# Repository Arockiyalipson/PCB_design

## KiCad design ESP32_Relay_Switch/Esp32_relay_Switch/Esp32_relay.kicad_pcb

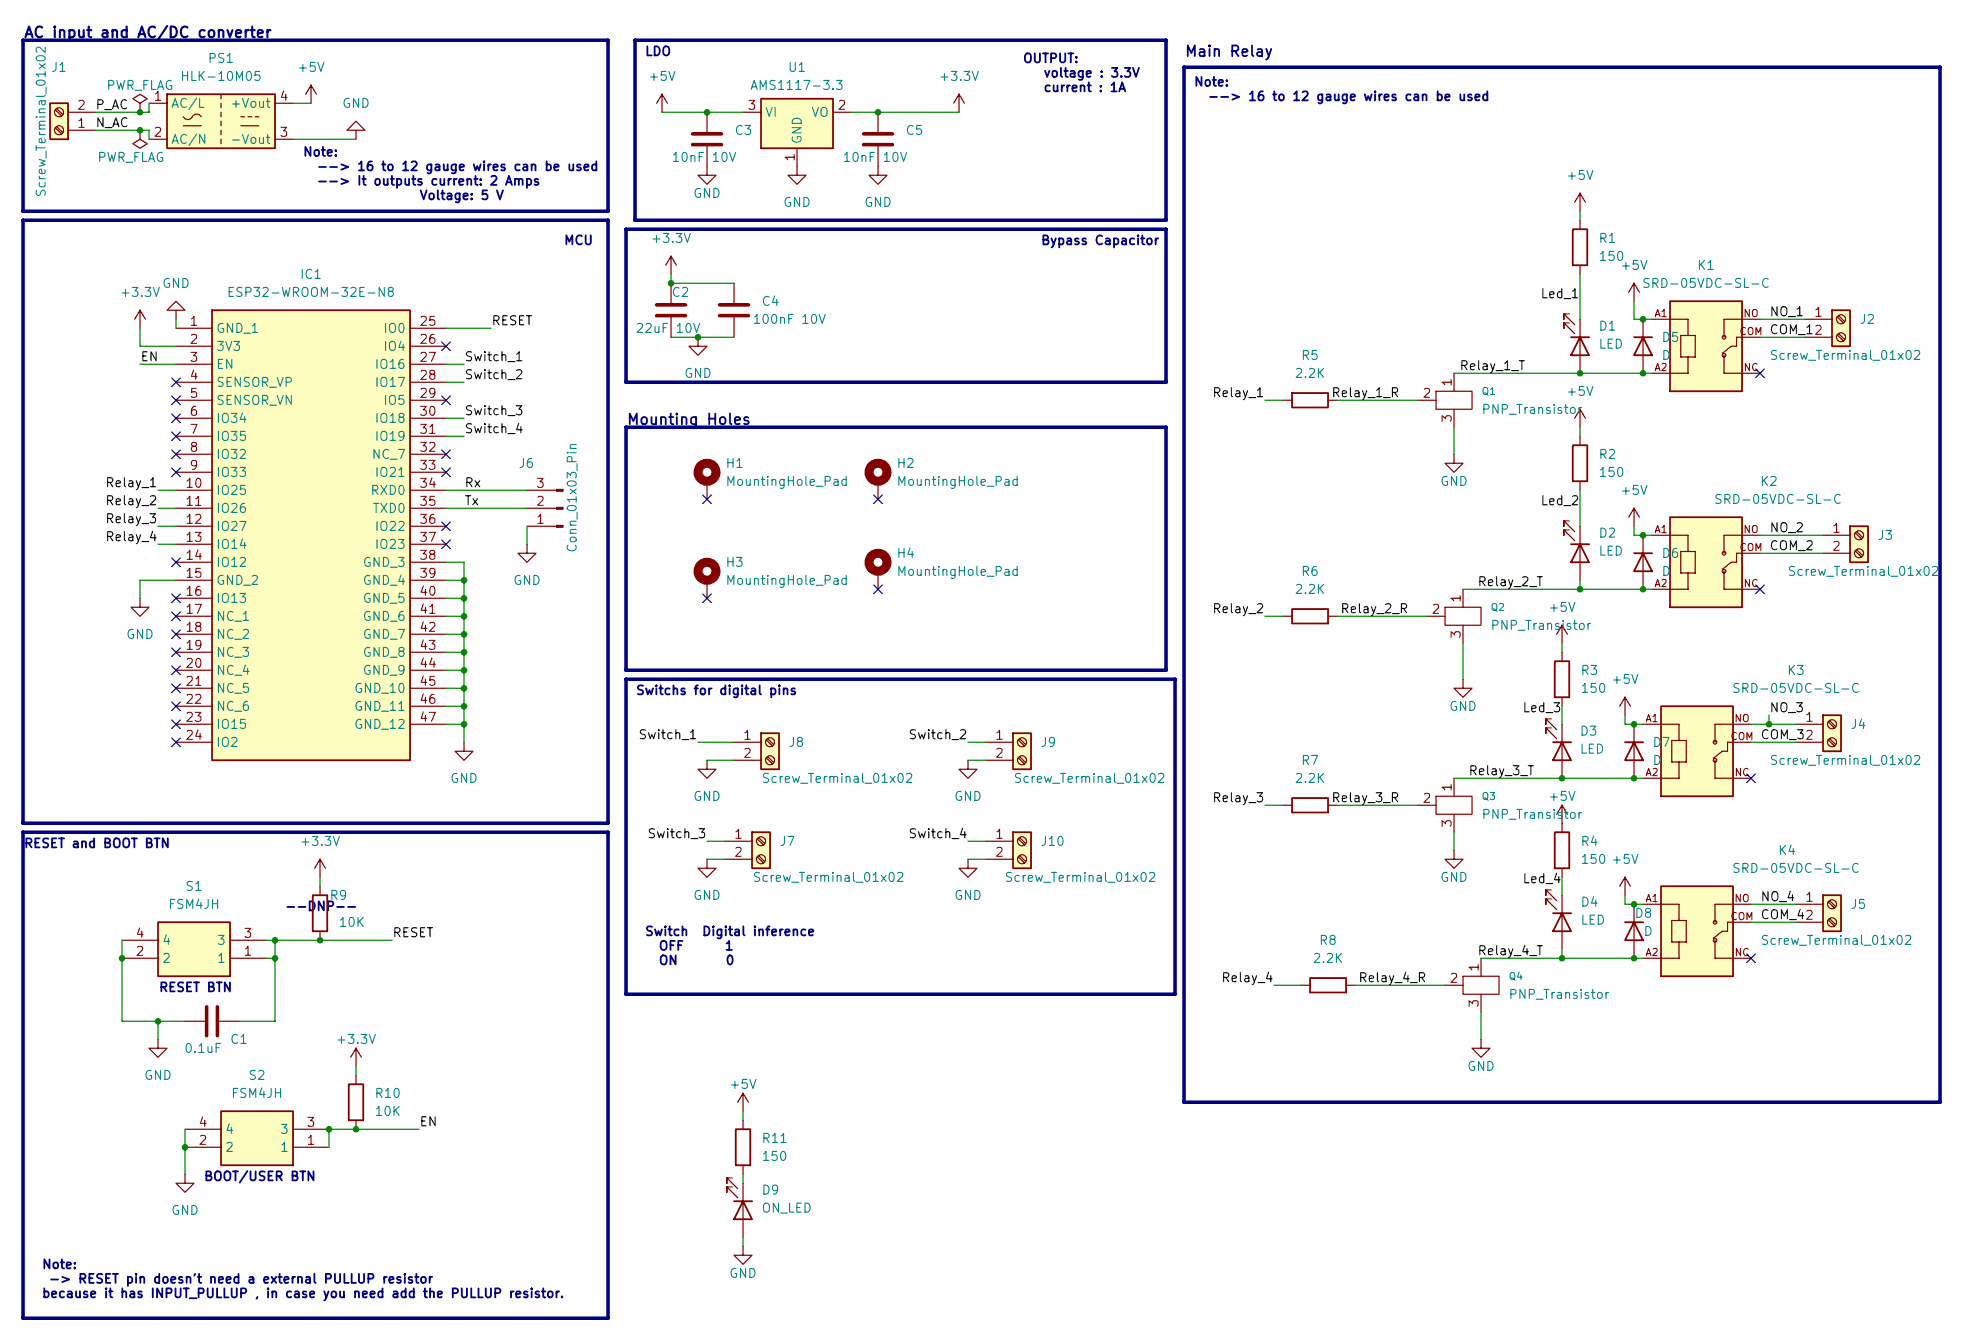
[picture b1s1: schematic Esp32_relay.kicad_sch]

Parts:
C1: 0.1uF; C_0805_2012Metric; Manufacturer_Part_Number C0805C104J8RACTU
C2: 22uF 10V; C_0805_2012Metric; Manufacturer_Part_Number CL21A226MPQNNNE
C3, C5: 10nF 10V; C_0805_2012Metric; Manufacturer_Part_Number 885012007009
C4: 100nF 10V; C_0805_2012Metric; Manufacturer_Part_Number C0805C104J5RAC
D1, D2, D3, D4: LED; LED_1206_3216Metric; Manufacturer_Part_Number 156120VS75000
D5, D6, D7, D8: D; D_0805_2012Metric; Manufacturer_Part_Number BZY55C9V1 RBG
D9: ON_LED; LED_1206_3216Metric; Manufacturer_Part_Number 156120VS75000
H1, H2, H3, H4: MountingHole_Pad; MountingHole_2.5mm_Pad; Manufacturer_Part_Number ----
IC1: ESP32-WROOM-32E-N8; ESP32WROOM32EN8; Mouser Part Number 356-ESP32WRM32E164PH
J1, J2, J3, J4, J5, J7, J8, J9, J10: Screw_Terminal_01x02; TerminalBlock_MetzConnect_Type175_RT02702HBLC_1x02_P7.50mm_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
J6: Conn_01x03_Pin; PinHeader_1x03_P2.54mm_Vertical; Manufacturer_Part_Number ----
K1, K2, K3, K4: SRD-05VDC-SL-C; RELAY_SRD-05VDC-SL-C; Manufacturer_Part_Number SRD-05VDC-SL-C
PS1: HLK-10M05; Converter_ACDC_HiLink_HLK-10Mxx; Manufacturer_Part_Number RW-317
Q1, Q2, Q3, Q4: PNP_Transistor; SOT-23; Manufacturer_Part_Number 5203
R1, R2, R3, R4, R11: 150; R_0805_2012Metric; Manufacturer_Part_Number CRCW0805150RFKEAC
R5, R6, R7, R8: 2.2K; R_0805_2012Metric; Manufacturer_Part_Number CRCW08052K20FKEA
R9, R10: 10K; R_0805_2012Metric; Manufacturer_Part_Number CR0805-FX-1002ELF
S1, S2: FSM4JH; Mouser Part Number 506-FSM4JH
U1: AMS1117-3.3; SOT-223-3_TabPin2; Manufacturer_Part_Number AMS1117-3.3

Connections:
+3.3V: C2.1, C4.1, C5.1, IC1.2 (3V3), R9.1, R10.1, U1.2 (VO)
+5V: C3.1, D5.1 (K), D6.1 (K), D7.1 (K), D8.1 (K), K1.A1, K2.A1, K3.A1, K4.A1, PS1.4 (+Vout), R1.1, R2.1, R3.1, R4.1, R11.1, U1.3 (VI)
/COM_1: J2.2, K1.COM
/COM_2: J3.2, K2.COM
/COM_3: J4.2, K3.COM
/COM_4: J5.2, K4.COM
/EN: IC1.3 (EN), R10.2, S2.1, S2.3
/Led_1: D1.1 (K), R1.2
/Led_2: D2.1 (K), R2.2
/Led_3: D3.1 (K), R3.2
/Led_4: D4.1 (K), R4.2
/NO_1: J2.1, K1.NO
/NO_2: J3.1, K2.NO
/NO_3: J4.1, K3.NO
/NO_4: J5.1, K4.NO
/N_AC: J1.1, PS1.2 (AC/N)
/P_AC: J1.2, PS1.1 (AC/L)
/RESET: C1.2, IC1.25 (IO0), R9.2, S1.1, S1.3
/Relay_1: IC1.10 (IO25), R5.2
/Relay_1_R: Q1.2, R5.1
/Relay_1_T: D1.2 (A), D5.2 (A), K1.A2, Q1.1
/Relay_2: IC1.11 (IO26), R6.1
/Relay_2_R: Q2.2, R6.2
/Relay_2_T: D2.2 (A), D6.2 (A), K2.A2, Q2.1
/Relay_3: IC1.12 (IO27), R7.1
/Relay_3_R: Q3.2, R7.2
/Relay_3_T: D3.2 (A), D7.2 (A), K3.A2, Q3.1
/Relay_4: IC1.13 (IO14), R8.1
/Relay_4_R: Q4.2, R8.2
/Relay_4_T: D4.2 (A), D8.2 (A), K4.A2, Q4.1
/Rx: IC1.34 (RXD0), J6.3
/Switch_1: IC1.27 (IO16), J8.1
/Switch_2: IC1.28 (IO17), J9.1
/Switch_3: IC1.30 (IO18), J7.1
/Switch_4: IC1.31 (IO19), J10.1
/Tx: IC1.35 (TXD0), J6.2
GND: C1.1, C2.2, C3.2, C4.2, C5.2, D9.2 (A), IC1.1 (GND_1), IC1.15 (GND_2), IC1.38 (GND_3), IC1.39 (GND_4), IC1.40 (GND_5), IC1.41 (GND_6), IC1.42 (GND_7), IC1.43 (GND_8), IC1.44 (GND_9), IC1.45 (GND_10), IC1.46 (GND_11), IC1.47 (GND_12), J6.1, J7.2, J8.2, J9.2, J10.2, PS1.3 (-Vout), Q1.3, Q2.3, Q3.3, Q4.3, S1.2, S1.4, S2.2, S2.4, U1.1 (GND)
unnamed: D9.1 (K), R11.2

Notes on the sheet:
Note: -> RESET pin doesn't need a external PULLUP resistor because it has INPUT_PULLUP , in case you need add the PULLUP resistor.
Main Relay
AC input and AC/DC converter
OUTPUT: voltage : 3.3V current : 1A
Switch Digital inference OFF 1 ON 0
RESET BTN
RESET and BOOT BTN
Switchs for digital pins
Note: --> 16 to 12 gauge wires can be used --> It outputs current: 2 Amps Voltage: 5 V
Note: --> 16 to 12 gauge wires can be used
Mounting Holes
--DNP--
Bypass Capacitor
MCU
LDO
BOOT/USER BTN

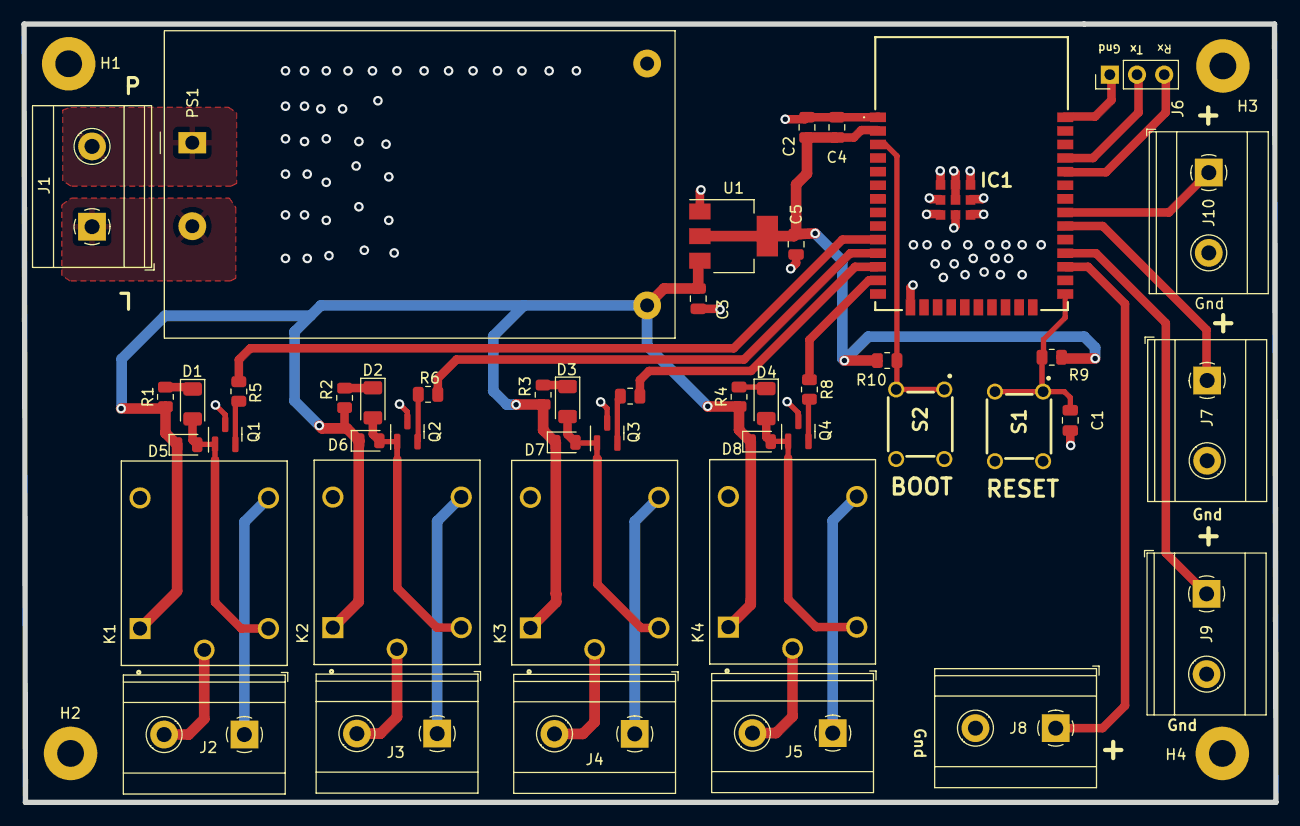
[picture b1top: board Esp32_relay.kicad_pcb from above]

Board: 2 copper layers, 117.0 x 72.7 mm, 50 parts (0 on the bottom side), 37 nets.

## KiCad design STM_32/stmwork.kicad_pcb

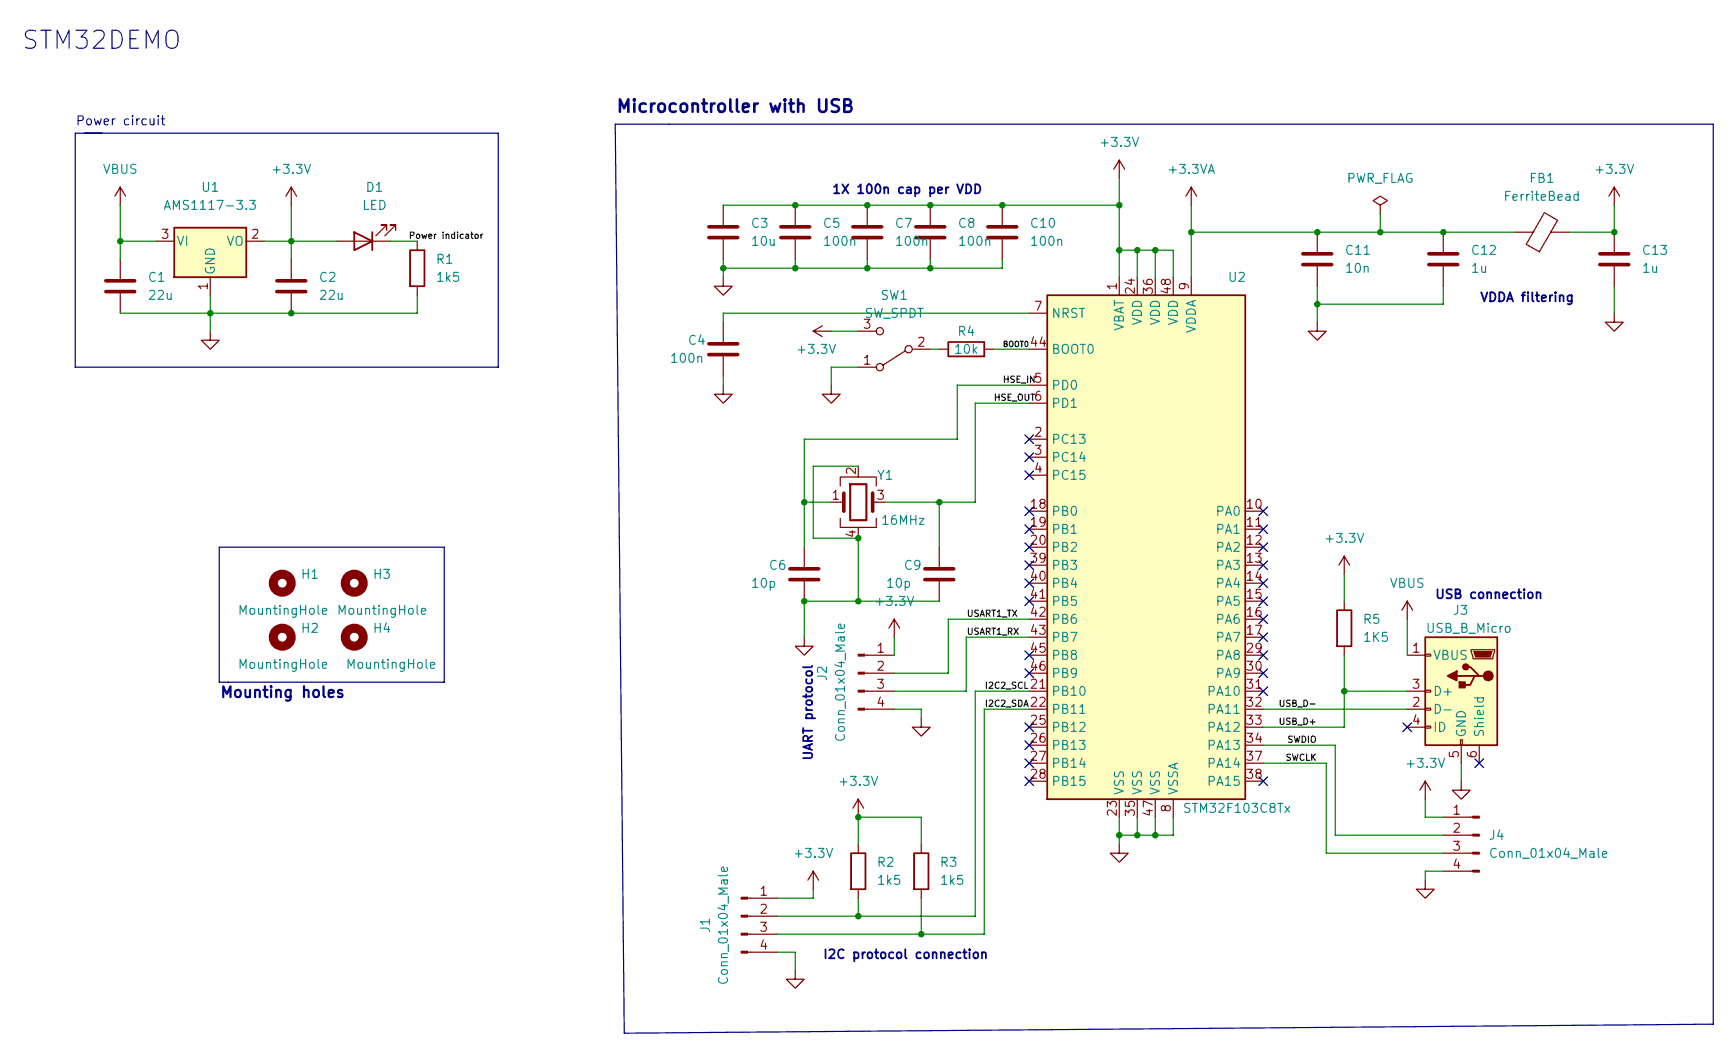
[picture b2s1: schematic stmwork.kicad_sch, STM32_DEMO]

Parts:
C1, C2: 22u; C_0805_2012Metric
C3: 10u; C_0603_1608Metric
C4, C5, C7, C8, C10: 100n; C_0603_1608Metric
C6, C9: 10p; C_0603_1608Metric
C11: 10n; C_0603_1608Metric
C12, C13: 1u; C_0603_1608Metric
D1: LED; LED_0603_1608Metric
FB1: FerriteBead; L_0603_1608Metric
H1, H2, H3, H4: MountingHole; MountingHole_2.1mm
J1, J2, J4: Conn_01x04_Male; PinHeader_1x04_P2.54mm_Vertical
J3: USB_B_Micro; USB_Micro-B_Wuerth_629105150521
R1, R2, R3: 1k5; R_0402_1005Metric
R4: 10k; R_0402_1005Metric
R5: 1K5; R_0402_1005Metric
SW1: SW_SPDT; SW_SPDT_PCM12
U1: AMS1117-3.3; SOT-223-3_TabPin2
U2: STM32F103C8Tx; LQFP-48_7x7mm_P0.5mm
Y1: 16MHz; Crystal_SMD_3225-4Pin_3.2x2.5mm

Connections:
+3.3V: C2.1, C3.1, C5.1, C7.1, C8.1, C10.1, C13.1, D1.2 (A), FB1.2, J1.1, J2.1, J4.1, R2.1, R3.1, R5.1, SW1.3 (C), U1.2 (VO), U2.1 (VBAT), U2.24 (VDD), U2.36 (VDD), U2.48 (VDD)
+3.3VA: C11.1, C12.2, FB1.1, U2.9 (VDDA)
/BOOT0: R4.2, U2.44 (BOOT0)
/HSE_IN: C6.1, U2.5 (PD0), Y1.1
/HSE_OUT: C9.1, U2.6 (PD1), Y1.3
/I2C2_SCL: J1.2, R2.2, U2.21 (PB10)
/I2C2_SDA: J1.3, R3.2, U2.22 (PB11)
/Power indicator: D1.1 (K), R1.1
/SWCLK: J4.3, U2.37 (PA14)
/SWDIO: J4.2, U2.34 (PA13)
/USART1_RX: J2.3, U2.43 (PB7)
/USART1_TX: J2.2, U2.42 (PB6)
/USB_D+: J3.3 (D+), R5.2, U2.33 (PA12)
/USB_D-: J3.2 (D-), U2.32 (PA11)
GND: C1.2, C2.2, C3.2, C4.2, C5.2, C6.2, C7.2, C8.2, C9.2, C10.2, C11.2, C12.1, C13.2, J1.4, J2.4, J3.5 (GND), J4.4, R1.2, SW1.1 (A), U1.1 (GND), U2.8 (VSSA), U2.23 (VSS), U2.35 (VSS), U2.47 (VSS), Y1.2, Y1.4
unnamed: C4.1, U2.7 (NRST)
unnamed: R4.1, SW1.2 (B)
VBUS: C1.1, J3.1 (VBUS), U1.3 (VI)

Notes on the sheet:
Microcontroller with USB
USB connection
VDDA filtering
I2C protocol connection
Power circuit
STM32DEMO
UART protocol
Mounting holes
1X 100n cap per VDD

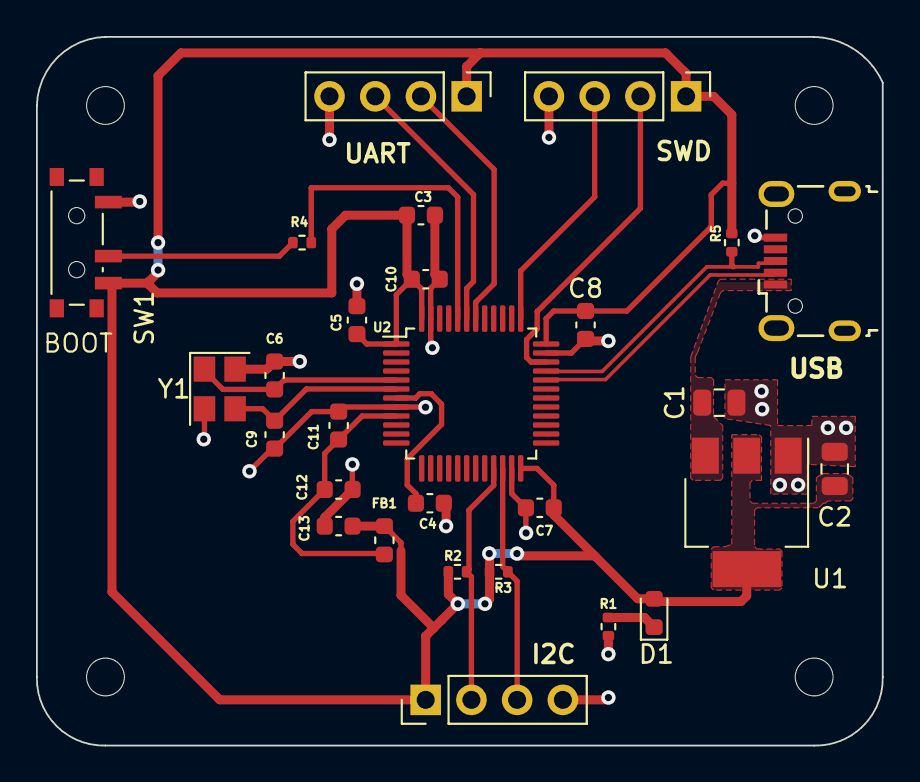
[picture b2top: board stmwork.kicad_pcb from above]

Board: 2 copper layers, 47.0 x 39.4 mm, 32 parts (0 on the bottom side), 18 nets.

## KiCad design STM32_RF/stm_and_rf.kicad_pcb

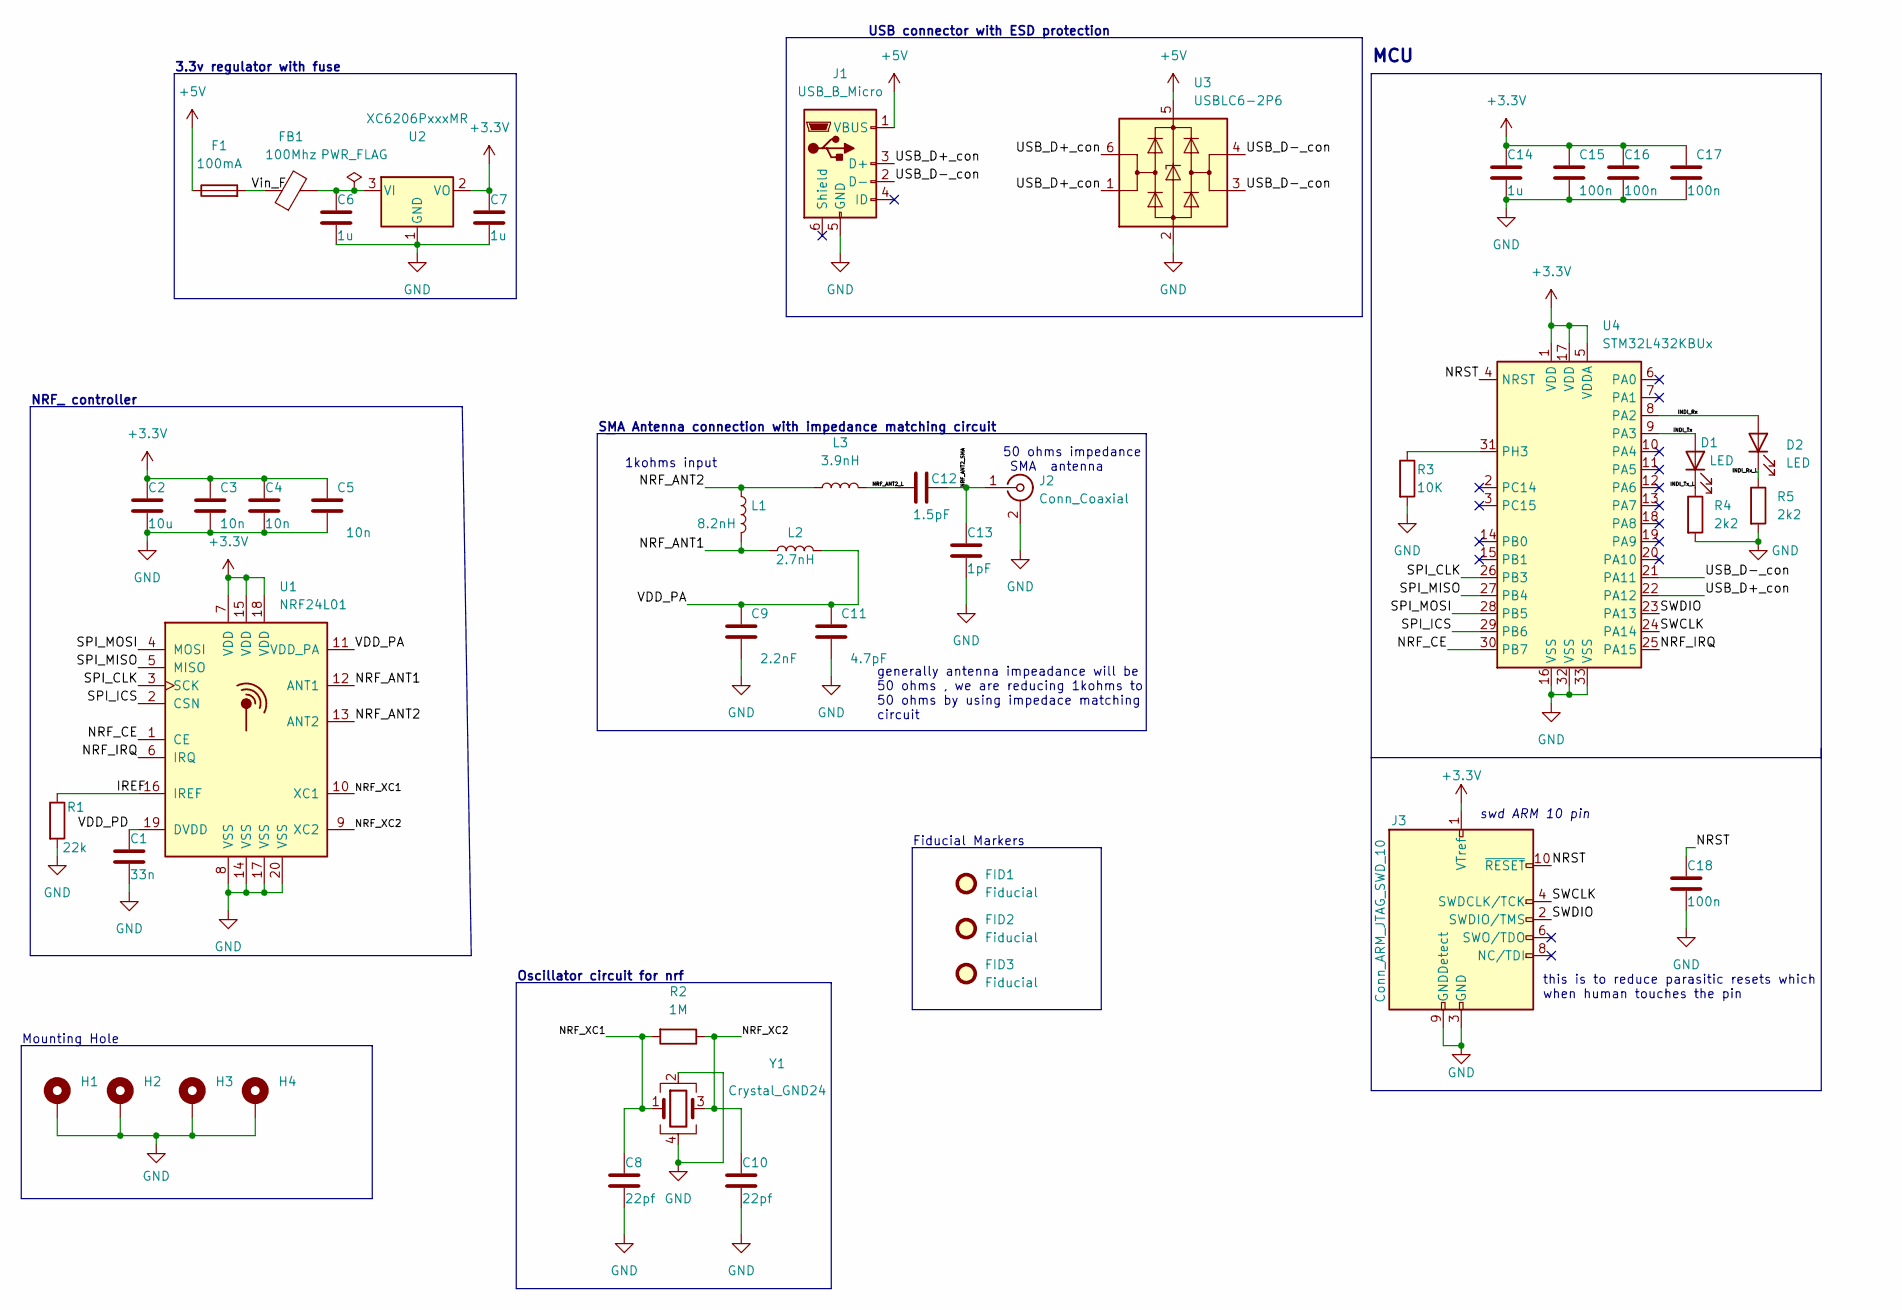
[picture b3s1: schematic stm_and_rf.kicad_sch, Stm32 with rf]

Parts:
C1: 33n; C_0402_1005Metric
C2: 10u; C_0402_1005Metric
C3, C4, C5: 10n; C_0402_1005Metric
C6, C7: 1u; C_0603_1608Metric
C8, C10: 22pf; C_0402_1005Metric
C9: 2.2nF; C_0402_1005Metric
C11: 4.7pF; C_0402_1005Metric
C12: 1.5pF; C_0402_1005Metric
C13: 1pF; C_0402_1005Metric
C14: 1u; C_0402_1005Metric
C15, C16, C17, C18: 100n; C_0402_1005Metric
D1, D2: LED; LED_0603_1608Metric
F1: 100mA; Fuse_1206_3216Metric
FB1: 100Mhz; L_0805_2012Metric
FID1, FID2, FID3: Fiducial; Fiducial_0.5mm_Mask1mm
H1, H2, H3, H4: MountingHole_Pad; MountingHole_2.2mm_M2_Pad
J1: USB_B_Micro; USB_Micro-B_Wuerth_629105150521
J2: Conn_Coaxial; SMA_Samtec_SMA-J-P-X-ST-EM1_EdgeMount
J3: Conn_ARM_JTAG_SWD_10; PinHeader_2x05_P1.27mm_Vertical
L1: 8.2nH; L_0402_1005Metric
L2: 2.7nH; L_0402_1005Metric
L3: 3.9nH; L_0402_1005Metric
R1: 22k; R_0402_1005Metric
R2: 1M; R_0402_1005Metric
R3: 10K; R_0402_1005Metric
R4, R5: 2k2; R_0402_1005Metric
U1: NRF24L01; QFN-20-1EP_4x4mm_P0.5mm_EP2.5x2.5mm
U2: XC6206PxxxMR; SOT-23
U3: USBLC6-2P6; SOT-666
U4: STM32L432KBUx; QFN-32-1EP_5x5mm_P0.5mm_EP3.45x3.45mm
Y1: Crystal_GND24; Crystal_SMD_3225-4Pin_3.2x2.5mm

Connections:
+3.3V: C2.1, C3.1, C4.1, C5.1, C7.1, C14.1, C15.1, C16.1, C17.1, J3.1 (VTref), U1.7 (VDD), U1.15 (VDD), U1.18 (VDD), U2.2 (VO), U4.1 (VDD), U4.5 (VDDA), U4.17 (VDD)
+5V: F1.1, J1.1 (VBUS), U3.5 (VBUS)
/INDI_Rx: D2.2 (A), U4.8 (PA2)
/INDI_Rx_L: D2.1 (K), R5.1
/INDI_Tx: D1.2 (A), U4.9 (PA3)
/INDI_Tx_L: D1.1 (K), R4.1
/IREF: R1.1, U1.16 (IREF)
/NRF_ANT1: L1.2, L2.1, U1.12 (ANT1)
/NRF_ANT2: L1.1, L3.1, U1.13 (ANT2)
/NRF_ANT2_L: C12.2, L3.2
/NRF_ANT2_SMA: C12.1, C13.1, J2.1 (In)
/NRF_CE: U1.1 (CE), U4.30 (PB7)
/NRF_IRQ: U1.6 (IRQ), U4.25 (PA15)
/NRF_XC1: C8.1, R2.2, U1.10 (XC1), Y1.1
/NRF_XC2: C10.1, R2.1, U1.9 (XC2), Y1.3
/NRST: C18.1, J3.10 (~RESET), U4.4 (NRST)
/SPI_CLK: U1.3 (SCK), U4.26 (PB3)
/SPI_ICS: U1.2 (CSN), U4.29 (PB6)
/SPI_MISO: U1.5 (MISO), U4.27 (PB4)
/SPI_MOSI: U1.4 (MOSI), U4.28 (PB5)
/SWCLK: J3.4 (SWDCLK/TCK), U4.24 (PA14)
/SWDIO: J3.2 (SWDIO/TMS), U4.23 (PA13)
/USB_D+_con: J1.3 (D+), U3.1 (I/O1), U3.6 (I/O1), U4.22 (PA12)
/USB_D-_con: J1.2 (D-), U3.3 (I/O2), U3.4 (I/O2), U4.21 (PA11)
/VDD_PA: C9.1, C11.1, L2.2, U1.11 (VDD_PA)
/VDD_PD: C1.1, U1.19 (DVDD)
/Vin_F: F1.2, FB1.1
GND: C1.2, C2.2, C3.2, C4.2, C5.2, C6.2, C7.2, C8.2, C9.2, C10.2, C11.2, C13.2, C14.2, C15.2, C16.2, C17.2, C18.2, H1.1, H2.1, H3.1, H4.1, J1.5 (GND), J2.2 (Ext), J3.3 (GND), J3.5 (GND), J3.9 (GNDDetect), R1.2, R3.2, R4.2, R5.2, U1.8 (VSS), U1.14 (VSS), U1.17 (VSS), U1.20 (VSS), U2.1 (GND), U3.2 (GND), U4.16 (VSS), U4.32 (VSS), U4.33 (VSS), Y1.2, Y1.4
unnamed: C6.1, FB1.2, U2.3 (VI)
unnamed: R3.1, U4.31 (PH3)

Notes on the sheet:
1kohms input
Fiducial Markers
swd ARM 10 pin
generally antenna impeadance will be 50 ohms , we are reducing 1kohms to 50 ohms by using impedace matching circuit
3.3v regulator with fuse
Mounting Hole
SMA Antenna connection with impedance matching circuit
MCU
USB connector with ESD protection
Oscillator circuit for nrf
this is to reduce parasitic resets which when human touches the pin
50 ohms impedance SMA antenna
NRF_ controller

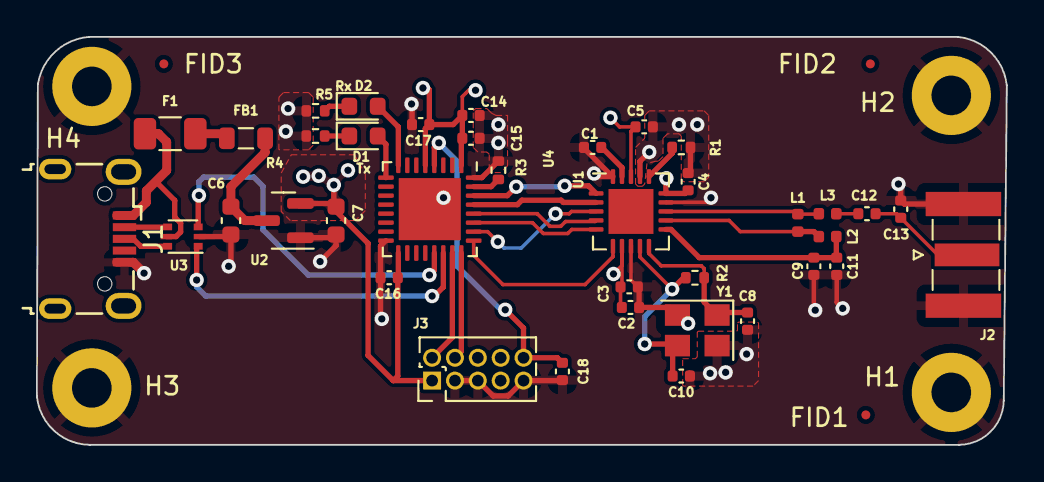
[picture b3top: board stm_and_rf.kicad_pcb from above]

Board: 4 copper layers, 53.9 x 22.7 mm, 45 parts (0 on the bottom side), 30 nets.

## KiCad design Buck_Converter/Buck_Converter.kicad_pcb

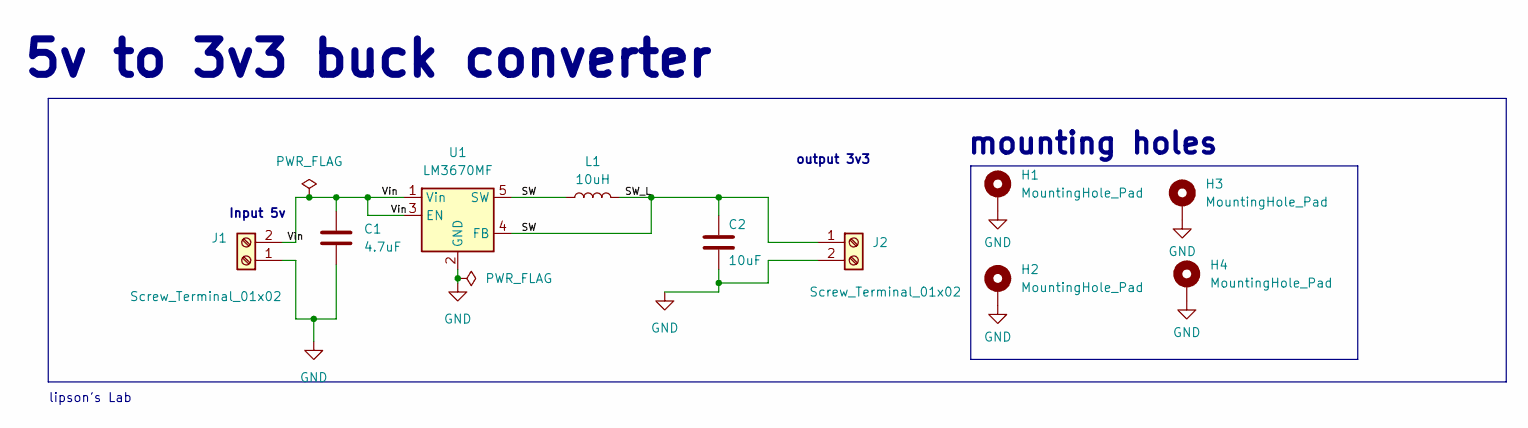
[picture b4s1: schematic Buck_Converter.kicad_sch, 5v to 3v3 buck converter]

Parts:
C1: 4.7uF; C_0805_2012Metric_Pad1.18x1.45mm_HandSolder
C2: 10uF; C_1206_3216Metric_Pad1.33x1.80mm_HandSolder
H1, H2, H3, H4: MountingHole_Pad; MountingHole_2.2mm_M2_DIN965_Pad
J1, J2: Screw_Terminal_01x02; TerminalBlock_Phoenix_MKDS-1,5-2-5.08_1x02_P5.08mm_Horizont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
L1: 10uH; VLCF4024T-100MR90-2
U1: LM3670MF; TSOT-23-5

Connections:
/SW: C2.1, J2.1, L1.1, L1.2, U1.4 (FB), U1.5 (SW)
/Vin: C1.1, J1.2, U1.1 (Vin), U1.3 (EN)
GND: C1.2, C2.2, H1.1, H2.1, H3.1, H4.1, J1.1, J2.2, U1.2 (GND)

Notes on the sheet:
lipson's Lab
Input 5v
output 3v3
mounting holes
5v to 3v3 buck converter

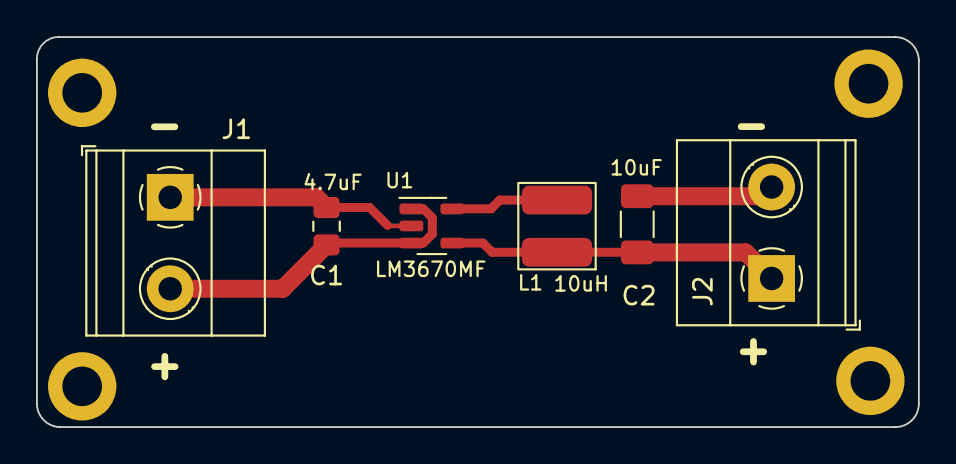
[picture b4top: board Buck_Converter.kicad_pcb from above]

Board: 2 copper layers, 49.0 x 21.7 mm, 10 parts (0 on the bottom side), 3 nets.

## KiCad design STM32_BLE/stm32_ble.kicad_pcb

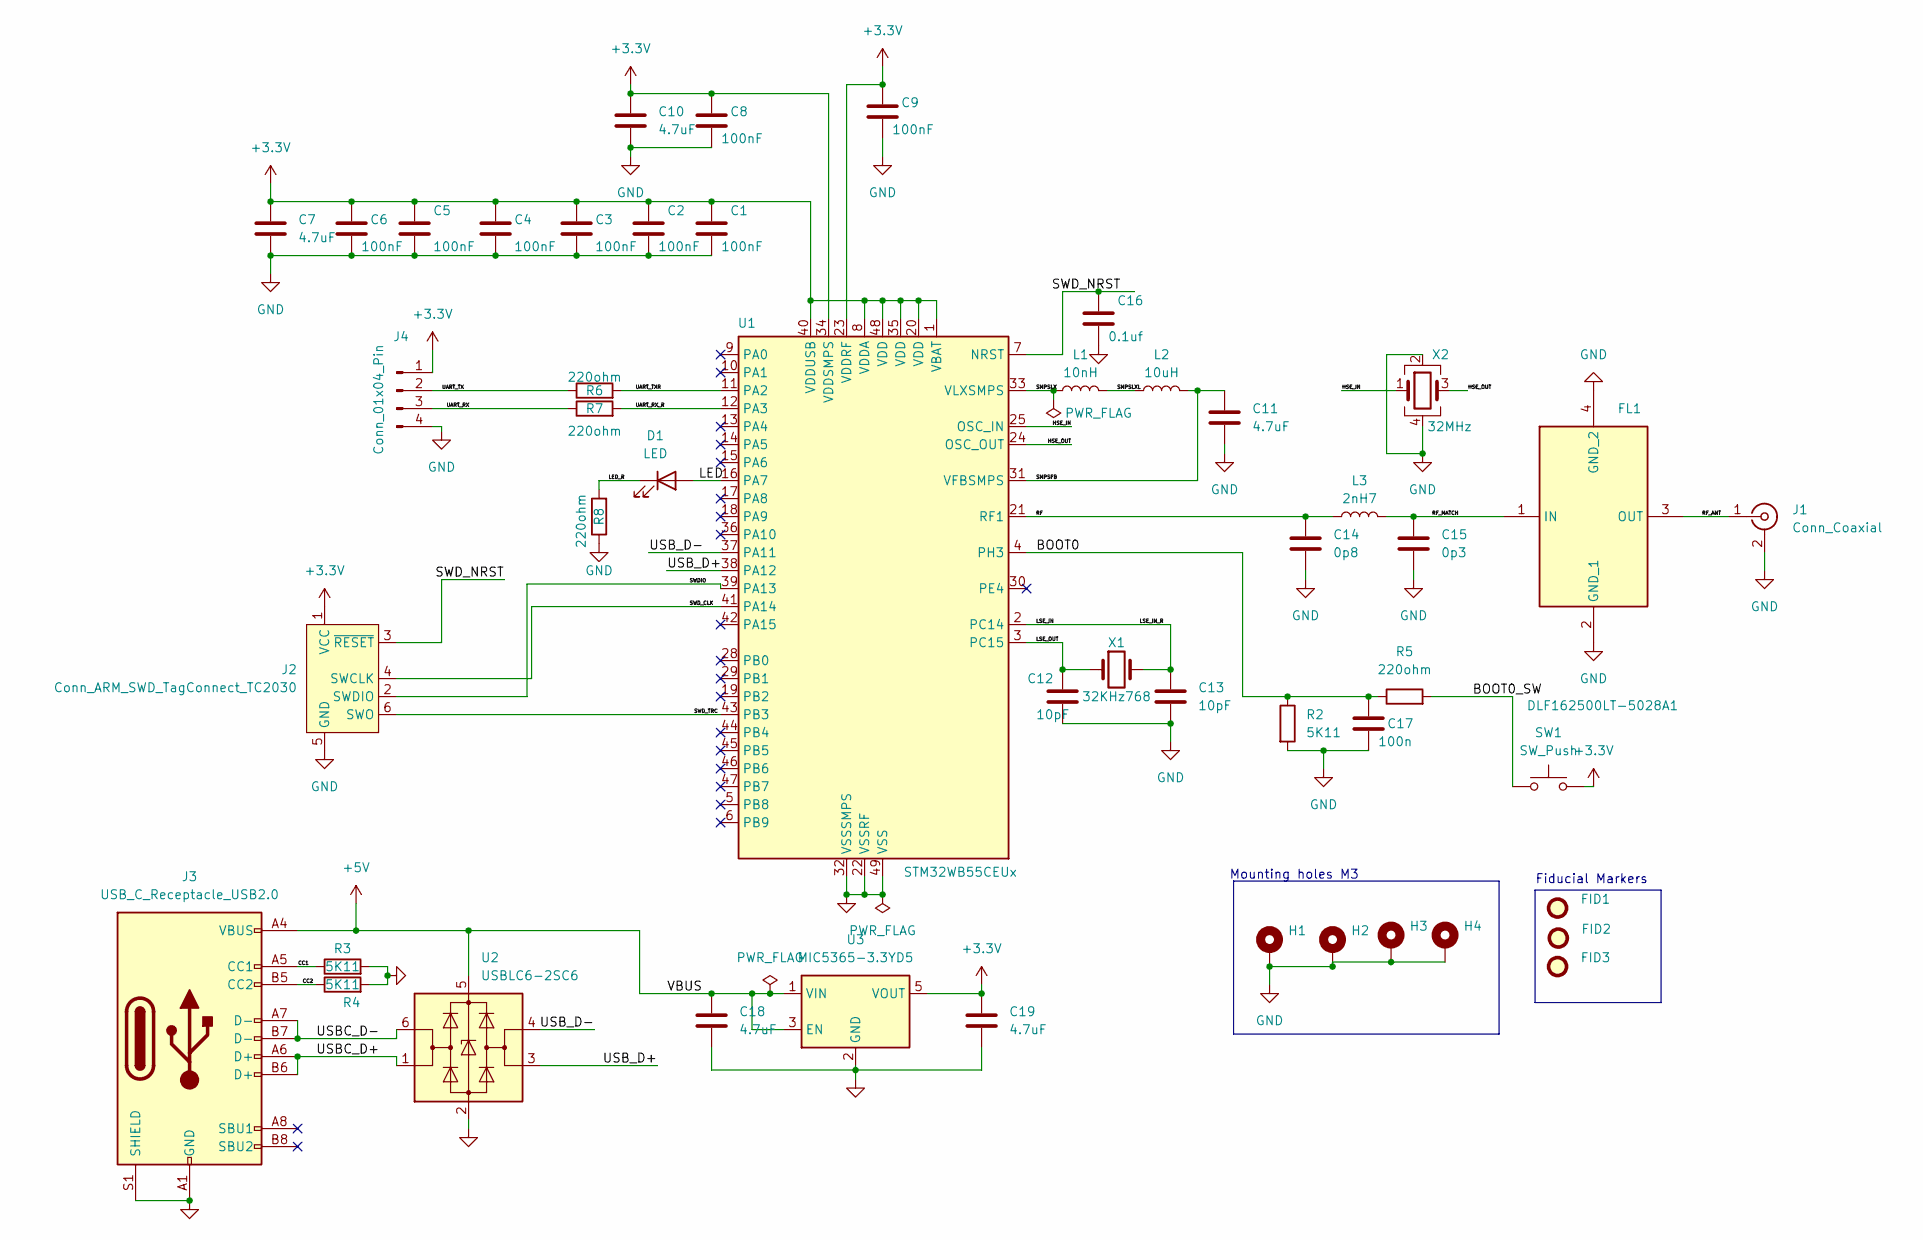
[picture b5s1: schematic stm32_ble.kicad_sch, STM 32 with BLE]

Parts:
C1, C2, C3, C4, C5, C6, C8, C9: 100nF; C_0402_1005Metric; Manufacturer_Part_Number VJ0402Y104KXXCW1BC
C7, C10, C11, C18: 4.7uF; C_0603_1608Metric; Manufacturer_Part_Number GCJ188C70J475KE02D
C12, C13: 10pF; C_0402_1005Metric; Manufacturer_Part_Number C0402C100K4GACAUTO
C14: 0p8; C_0402_1005Metric; Manufacturer_Part_Number GRM0335C1HR80BA01D
C15: 0p3; C_0402_1005Metric; Manufacturer_Part_Number GRM1555C1HR30WA01D
C16: 0.1uf; C_0402_1005Metric; Manufacturer_Part_Number C0402C104K4RACTU
C17: 100n; C_0402_1005Metric; Manufacturer_Part_Number CC0402KRX7R7BB104
C19: 4.7uF; C_0402_1005Metric; Manufacturer_Part_Number GRT155C81A475ME13J
D1: LED; LED_0402_1005Metric; Manufacturer_Part_Number 150040RS73240
FID1, FID2, FID3: Fiducial; Fiducial_1mm_Mask2mm
FL1: DLF162500LT-5028A1; DLF162500LT5028A1; Mouser Part Number 810-DLF16250LT5028A1
H1, H2, H3, H4: MountingHole_Pad; MountingHole_2.2mm_M2_Pad_Via
J1: Conn_Coaxial; U.FL_Hirose_U.FL-R-SMT-1_Vertical; Manufacturer_Part_Number U.FL-R-SMT(01)
J2: Conn_ARM_SWD_TagConnect_TC2030; Tag-Connect_TC2030-IDC-FP_2x03_P1.27mm_Vertical
J3: USB_C_Receptacle_USB2.0; USB_C_Receptacle_GCT_USB4105-xx-A_16P_TopMnt_Horizontal; Manufacturer_Part_Number USB4105-GF-A
J4: Conn_01x04_Pin; Molex_PicoBlade_53048-0410_1x04_P1.25mm_Horizontal; Manufacturer_Part_Number 53048-0410
L1: 10nH; L_0402_1005Metric; Manufacturer_Part_Number LQG15WZ10NJ02D
L2: 10uH; L_0805_2012Metric; Manufacturer_Part_Number LQG15WZ10NJ02D
L3: 2nH7; L_0402_1005Metric; Manufacturer_Part_Number LQG15HS2N7S02D
R2, R3, R4: 5K11; R_0402_1005Metric; Manufacturer_Part_Number RC0402FR-075K1L
R5, R6, R7, R8: 220ohm; R_0402_1005Metric; Manufacturer_Part_Number MCS04020C2200FE000
SW1: SW_Push; SW_SPST_CK_RS282G05A3; Manufacturer_Part_Number RS282G05A3SMRT
U1: STM32WB55CEUx; QFN-48-1EP_7x7mm_P0.5mm_EP5.6x5.6mm; Manufacturer_Part_Number STM32WB55CEU6
U2: USBLC6-2SC6; SOT-23-6; Manufacturer_Part_Number USBLC6-2SC6
U3: MIC5365-3.3YD5; SOT-23-5; Manufacturer_Part_Number MIC5365-3.3YD5-TR
X1: 32KHz768; Crystal_SMD_2012-2Pin_2.0x1.2mm; Manufacturer_Part_Number NX2012SA-32.768K-STD-MUB-1
X2: 32MHz; Crystal_SMD_2016-4Pin_2.0x1.6mm; Manufacturer_Part_Number NX2016SA-32M-EXS00A-CS06465

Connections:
+3.3V: C1.1, C2.1, C3.1, C4.1, C5.1, C6.1, C7.1, C8.1, C9.1, C10.1, C19.1, J2.1 (VCC), J4.1, SW1.2, U1.1 (VBAT), U1.8 (VDDA), U1.20 (VDD), U1.23 (VDDRF), U1.34 (VDDSMPS), U1.35 (VDD), U1.40 (VDDUSB), U1.48 (VDD), U3.5 (VOUT)
+5V: C18.1, J3.A4 (VBUS), J3.A9 (VBUS), J3.B4 (VBUS), J3.B9 (VBUS), U2.5 (VBUS), U3.1 (VIN), U3.3 (EN)
/BOOT0: C17.1, R2.1, R5.1, U1.4 (PH3)
/BOOT0_SW: R5.2, SW1.1
/CC1: J3.A5 (CC1), R3.1
/CC2: J3.B5 (CC2), R4.1
/HSE_IN: U1.25 (OSC_IN), X2.1
/HSE_OUT: U1.24 (OSC_OUT), X2.3
/LED: D1.2 (A), U1.16 (PA7)
/LED_R: D1.1 (K), R8.2
/LSE_IN: C13.1, U1.2 (PC14), X1.2
/LSE_OUT: C12.1, U1.3 (PC15), X1.1
/RF: C14.1, L3.1, U1.21 (RF1)
/RF_ANT: FL1.3 (OUT), J1.1 (In)
/RF_MATCH: C15.1, FL1.1 (IN), L3.2
/SMPSFB: C11.1, L2.2, U1.31 (VFBSMPS)
/SMPSLX: L1.1, U1.33 (VLXSMPS)
/SMPSLXL: L1.2, L2.1
/SWDIO: J2.2 (SWDIO), U1.39 (PA13)
/SWD_CLK: J2.4 (SWCLK), U1.41 (PA14)
/SWD_NRST: C16.1, J2.3 (~RESET), U1.7 (NRST)
/SWD_TRC: J2.6 (SWO), U1.43 (PB3)
/UART_RX: J4.3, R7.1
/UART_RX_R: R7.2, U1.12 (PA3)
/UART_TX: J4.2, R6.1
/UART_TXR: R6.2, U1.11 (PA2)
/USBC_D+: J3.A6 (D+), J3.B6 (D+), U2.1 (I/O1)
/USBC_D-: J3.A7 (D-), J3.B7 (D-), U2.6 (I/O1)
/USB_D+: U1.38 (PA12), U2.3 (I/O2)
/USB_D-: U1.37 (PA11), U2.4 (I/O2)
GND: C1.2, C2.2, C3.2, C4.2, C5.2, C6.2, C7.2, C8.2, C9.2, C10.2, C11.2, C12.2, C13.2, C14.2, C15.2, C16.2, C17.2, C18.2, C19.2, FL1.2 (GND_1), FL1.4 (GND_2), H1.1, H2.1, H3.1, H4.1, J1.2 (Ext), J2.5 (GND), J3.A1 (GND), J3.A12 (GND), J3.B1 (GND), J3.B12 (GND), J3.S1 (SHIELD), J4.4, R2.2, R3.2, R4.2, R8.1, U1.22 (VSSRF), U1.32 (VSSSMPS), U1.49 (VSS), U2.2 (GND), U3.2 (GND), X2.2, X2.4

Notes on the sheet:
Fiducial Markers
Mounting holes M3

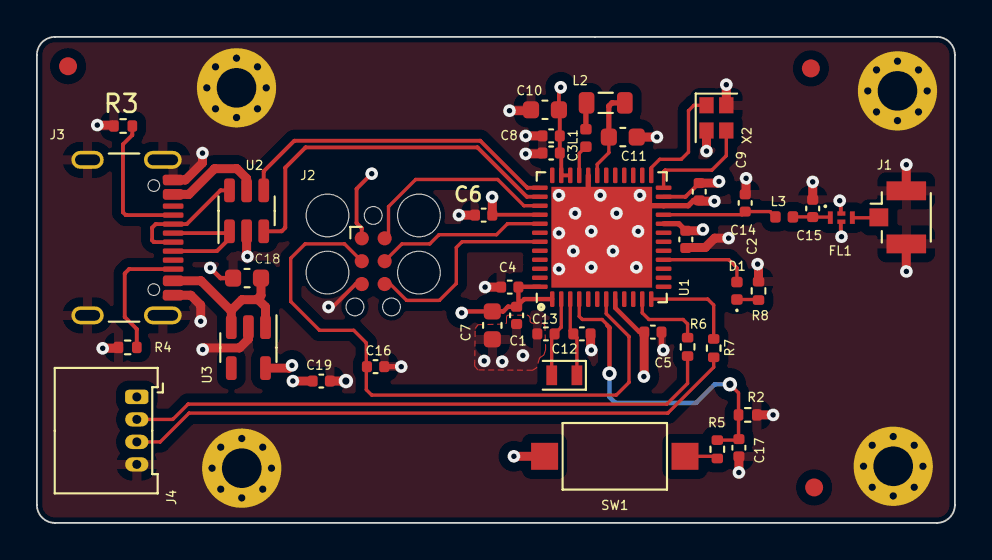
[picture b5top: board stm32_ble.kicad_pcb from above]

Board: 4 copper layers, 51.0 x 27.0 mm, 48 parts (0 on the bottom side), 31 nets.
